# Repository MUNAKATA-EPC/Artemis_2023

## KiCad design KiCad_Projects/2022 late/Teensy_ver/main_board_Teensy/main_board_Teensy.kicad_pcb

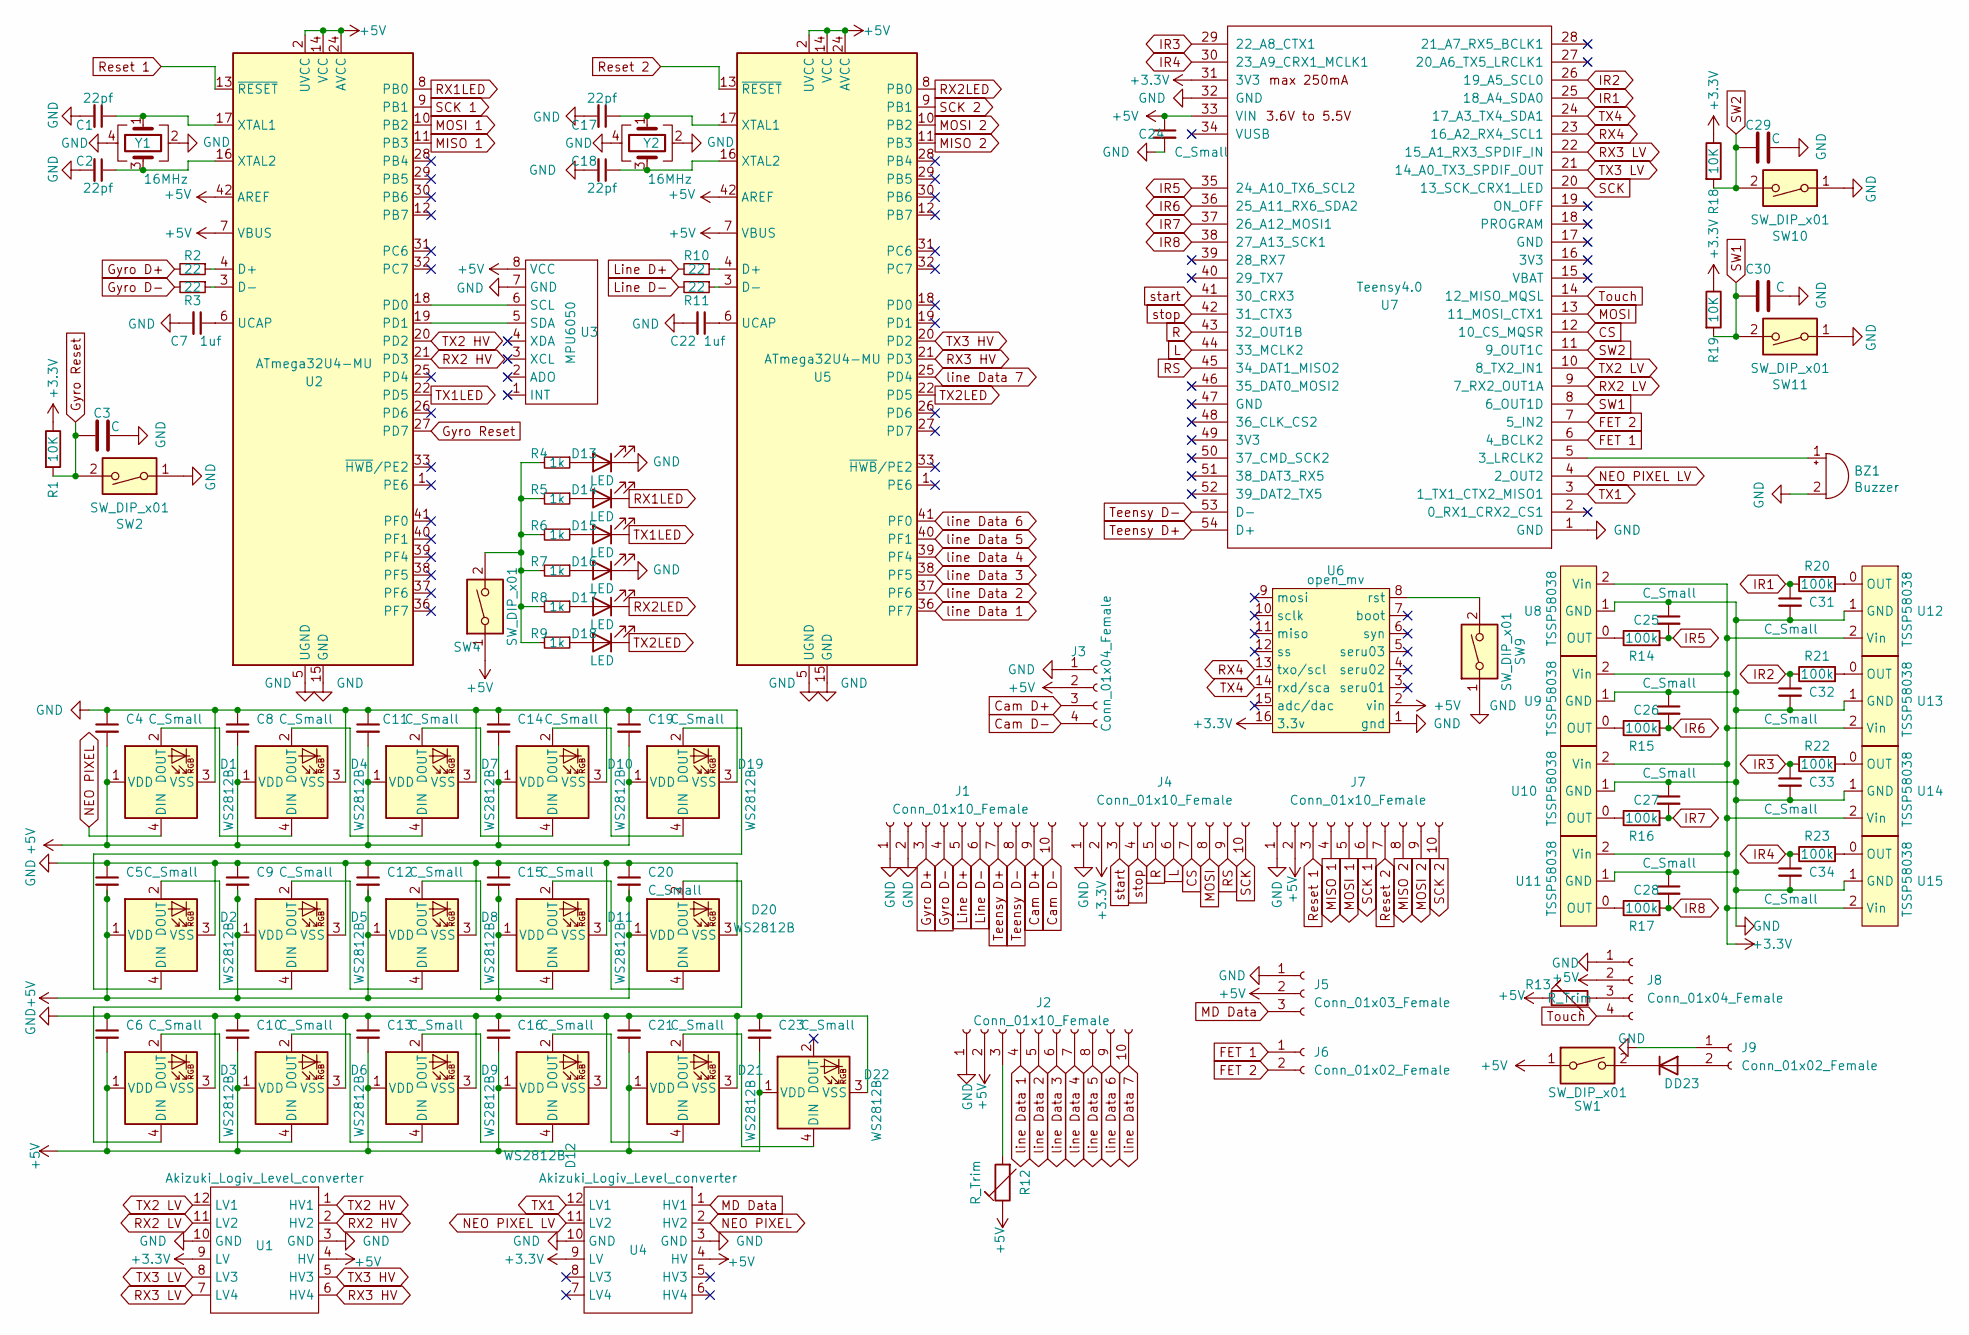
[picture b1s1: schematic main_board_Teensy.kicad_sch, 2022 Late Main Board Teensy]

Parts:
BZ1: Buzzer; Buzzer_12x9.5RM7.6
C1, C2, C17, C18: 22pf; C_0402_1005Metric; LCSC C1555
C3, C29, C30: C; C_0402_1005Metric; LCSC C507422
C4, C5, C6, C8, C9, C10, C11, C12, C13, C14, C15, C16, C19, C20, C21, C23, C24, C25, C26, C27, C28, C31, C32, C33, C34: C_Small; C_0402_1005Metric; LCSC C507422
C7, C22: 1uf; C_0402_1005Metric; LCSC C52923
D1, D2, D3, D5, D6, D7, D8, D9, D10, D11, D12, D19, D20, D21, D22: WS2812B; LED_WS2812B_PLCC4_5.0x5.0mm_P3.2mm; LCSC C2761795
D4: WS2812B; LED_WS2812B_PLCC4_5.0x5.0mm_P3.2mm
D13, D14, D15, D16, D17, D18: LED; LED_0402_1005Metric; LCSC C130725
D23: D; D_A-405_P7.62mm_Horizontal
J1, J4, J7: Conn_01x10_Female; PinHeader_1x10_P2.54mm_Vertical
J2: Conn_01x10_Female; JST_XH_S10B-XH-A-1_1x10_P2.50mm_Horizontal
J3: Conn_01x04_Female; PinHeader_1x04_P2.54mm_Vertical
J5: Conn_01x03_Female; JST_XH_B3B-XH-A_1x03_P2.50mm_Vertical
J6, J9: Conn_01x02_Female; JST_XH_B2B-XH-A_1x02_P2.50mm_Vertical
J8: Conn_01x04_Female; JST_XH_B4B-XH-A_1x04_P2.50mm_Vertical
R1, R18, R19: 10K; R_0402_1005Metric; LCSC C269674
R2, R3, R10, R11: 22; R_0402_1005Metric; LCSC C25092
R4, R5, R6, R7, R8, R9: 1k; R_0402_1005Metric; LCSC C11702
R12, R13: R_Trim; 可変抵抗(小)
R14, R15, R16, R17, R20, R21, R22, R23: 100k; R_0402_1005Metric; LCSC C269673
SW1, SW4: SW_DIP_x01; 2MS1T2B4M2QES
SW2, SW9, SW10, SW11: SW_DIP_x01; SW_PUSH_6mm_H5mm
U1, U4: Akizuki_Logiv_Level_converter; Akizuki_Logic_Level_converter
U2, U5: ATmega32U4-MU; QFN-44-1EP_7x7mm_P0.5mm_EP5.2x5.2mm; LCSC C112161
U3: MPU6050
U6: open_mv; OpenMV
U7: Teensy4.0; Teensy_Brakeout
U8, U9, U10, U11, U12, U13, U14, U15: TSSP58038; TSSP58038_IR
Y1, Y2: 16MHz; Crystal_SMD_3225-4Pin_3.2x2.5mm; LCSC C164049

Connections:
+3V3: J4.2, R1.1, R18.1, R19.1, U1.9 (LV), U4.9 (LV), U6.16 (3.3v), U7.31 (3V3), U8.2 (Vin), U9.2 (Vin), U10.2 (Vin), U11.2 (Vin), U12.2 (Vin), U13.2 (Vin), U14.2 (Vin), U15.2 (Vin)
+5V: C4.2, C5.2, C6.2, C8.2, C9.2, C10.2, C11.2, C12.2, C13.2, C14.2, C15.2, C16.2, C19.2, C20.2, C21.2, C23.2, C24.1, D1.1 (VDD), D2.1 (VDD), D3.1 (VDD), D4.1 (VDD), D5.1 (VDD), D6.1 (VDD), D7.1 (VDD), D8.1 (VDD), D9.1 (VDD), D10.1 (VDD), D11.1 (VDD), D12.1 (VDD), D19.1 (VDD), D20.1 (VDD), D21.1 (VDD), D22.1 (VDD), J2.2, J3.2, J5.2, J7.2, J8.2, R12.1, R13.1, SW1.1, SW4.1, U1.4 (HV), U2.2 (UVCC), U2.7 (VBUS), U2.14 (VCC), U2.24 (AVCC), U2.34 (VCC), U2.42 (AREF), U2.44 (AVCC), U3.8 (VCC), U4.4 (HV), U5.2 (UVCC), U5.7 (VBUS), U5.14 (VCC), U5.24 (AVCC), U5.34 (VCC), U5.42 (AREF), U5.44 (AVCC), U6.2 (vin), U7.33 (VIN)
CS: J4.7, U7.12 (10_CS_MQSR)
Cam D+: J1.9, J3.3
Cam D-: J1.10, J3.4
FET 1: J6.1, U7.6 (4_BCLK2)
FET 2: J6.2, U7.7 (5_IN2)
GND: BZ1.2 (+), C1.2, C2.2, C3.2, C4.1, C5.1, C6.1, C7.2, C8.1, C9.1, C10.1, C11.1, C12.1, C13.1, C14.1, C15.1, C16.1, C17.2, C18.2, C19.1, C20.1, C21.1, C22.2, C23.1, C24.2, C25.1, C26.1, C27.1, C28.1, C29.2, C30.2, C31.2, C32.2, C33.2, C34.2, D1.3 (VSS), D2.3 (VSS), D3.3 (VSS), D4.3 (VSS), D5.3 (VSS), D6.3 (VSS), D7.3 (VSS), D8.3 (VSS), D9.3 (VSS), D10.3 (VSS), D11.3 (VSS), D12.3 (VSS), D13.1 (K), D16.1 (K), D19.3 (VSS), D20.3 (VSS), D21.3 (VSS), D22.3 (VSS), J1.1, J1.2, J2.1, J3.1, J4.1, J5.1, J7.1, J8.1, J9.1, SW2.1, SW9.1, SW10.1, SW11.1, U1.3 (GND), U1.10 (GND), U2.5 (UGND), U2.15 (GND), U2.23 (GND), U2.35 (GND), U2.43 (GND), U2.45 (GND), U3.7 (GND), U4.3 (GND), U4.10 (GND), U5.5 (UGND), U5.15 (GND), U5.23 (GND), U5.35 (GND), U5.43 (GND), U5.45 (GND), U6.1 (gnd), U7.1 (GND), U7.32 (GND), U8.1 (GND), U9.1 (GND), U10.1 (GND), U11.1 (GND), U12.1 (GND), U13.1 (GND), U14.1 (GND), U15.1 (GND), Y1.2, Y1.4, Y2.2, Y2.4
Gyro D+: J1.3, R2.2
Gyro D-: J1.4, R3.2
Gyro Reset: C3.1, R1.2, SW2.2, U2.27 (PD7)
IR1: C31.1, R20.1, U7.25 (18_A4_SDA0)
IR2: C32.1, R21.1, U7.26 (19_A5_SCL0)
IR3: C33.1, R22.1, U7.29 (22_A8_CTX1)
IR4: C34.1, R23.1, U7.30 (23_A9_CRX1_MCLK1)
IR5: C25.2, R14.2, U7.35 (24_A10_TX6_SCL2)
IR6: C26.2, R15.2, U7.36 (25_A11_RX6_SDA2)
IR7: C27.2, R16.2, U7.37 (26_A12_MOSI1)
IR8: C28.2, R17.2, U7.38 (27_A13_SCK1)
L: J4.6, U7.44 (33_MCLK2)
Line D+: J1.5, R10.2
Line D-: J1.6, R11.2
MD Data: J5.3, U4.1 (HV1)
MISO 1: J7.4, U2.11 (PB3)
MISO 2: J7.8, U5.11 (PB3)
MOSI: J4.8, U7.13 (11_MOSI_CTX1)
MOSI 1: J7.5, U2.10 (PB2)
MOSI 2: J7.9, U5.10 (PB2)
NEO PIXEL: D1.4 (DIN), U4.2 (HV2)
NEO PIXEL LV: U4.11 (LV2), U7.4 (2_OUT2)
unnamed: BZ1.1 (-), U7.5 (3_LRCLK2)
unnamed: C1.1, U2.17 (XTAL1), Y1.1
unnamed: C2.1, U2.16 (XTAL2), Y1.3
unnamed: C7.1, U2.6 (UCAP)
unnamed: C17.1, U5.17 (XTAL1), Y2.1
unnamed: C18.1, U5.16 (XTAL2), Y2.3
unnamed: C22.1, U5.6 (UCAP)
unnamed: D1.2 (DOUT), D4.4 (DIN)
unnamed: D2.2 (DOUT), D5.4 (DIN)
unnamed: D3.2 (DOUT), D6.4 (DIN)
unnamed: D4.2 (DOUT), D7.4 (DIN)
unnamed: D5.2 (DOUT), D8.4 (DIN)
unnamed: D6.2 (DOUT), D9.4 (DIN)
unnamed: D10.2 (DOUT), D19.4 (DIN)
unnamed: D7.2 (DOUT), D10.4 (DIN)
unnamed: D11.2 (DOUT), D20.4 (DIN)
unnamed: D8.2 (DOUT), D11.4 (DIN)
unnamed: D12.2 (DOUT), D21.4 (DIN)
unnamed: D9.2 (DOUT), D12.4 (DIN)
unnamed: D13.2 (A), R4.1
unnamed: D14.2 (A), R5.1
unnamed: D15.2 (A), R6.1
unnamed: D16.2 (A), R7.1
unnamed: D17.2 (A), R8.1
unnamed: D18.2 (A), R9.1
unnamed: D2.4 (DIN), D19.2 (DOUT)
unnamed: D3.4 (DIN), D20.2 (DOUT)
unnamed: D21.2 (DOUT), D22.4 (DIN)
unnamed: D23.1 (K), SW1.2
unnamed: D23.2 (A), J9.2
unnamed: J2.3, R12.2
unnamed: J8.3, R13.2
unnamed: R2.1, U2.4 (D+)
unnamed: R3.1, U2.3 (D-)
unnamed: R4.2, R5.2, R6.2, R7.2, R8.2, R9.2, SW4.2
unnamed: R10.1, U5.4 (D+)
unnamed: R11.1, U5.3 (D-)
unnamed: R14.1, U8.0 (OUT)
unnamed: R15.1, U9.0 (OUT)
unnamed: R16.1, U10.0 (OUT)
unnamed: R17.1, U11.0 (OUT)
unnamed: R20.2, U12.0 (OUT)
unnamed: R21.2, U13.0 (OUT)
unnamed: R22.2, U14.0 (OUT)
unnamed: R23.2, U15.0 (OUT)
unnamed: U2.18 (PD0), U3.6 (SCL)
unnamed: U2.19 (PD1), U3.5 (SDA)
unnamed: SW9.2, U6.8 (rst)
R: J4.5, U7.43 (32_OUT1B)
RS: J4.9, U7.45 (34_DAT1_MISO2)
RX1LED: D14.1 (K), U2.8 (PB0)
RX2 HV: U1.2 (HV2), U2.21 (PD3)
RX2 LV: U1.11 (LV2), U7.9 (7_RX2_OUT1A)
RX2LED: D17.1 (K), U5.8 (PB0)
RX3 HV: U1.6 (HV4), U5.21 (PD3)
RX3 LV: U1.7 (LV4), U7.22 (15_A1_RX3_SPDIF_IN)
RX4: U6.13 (txo/scl), U7.23 (16_A2_RX4_SCL1)
Reset 1: J7.3, U2.13 (~RESET)
Reset 2: J7.7, U5.13 (~RESET)
SCK: J4.10, U7.20 (13_SCK_CRX1_LED)
SCK 1: J7.6, U2.9 (PB1)
SCK 2: J7.10, U5.9 (PB1)
SW1: C30.1, R19.2, SW11.2, U7.8 (6_OUT1D)
SW2: C29.1, R18.2, SW10.2, U7.11 (9_OUT1C)
TX1: U4.12 (LV1), U7.3 (1_TX1_CTX2_MISO1)
TX1LED: D15.1 (K), U2.22 (PD5)
TX2 HV: U1.1 (HV1), U2.20 (PD2)
TX2 LV: U1.12 (LV1), U7.10 (8_TX2_IN1)
TX2LED: D18.1 (K), U5.22 (PD5)
TX3 HV: U1.5 (HV3), U5.20 (PD2)
TX3 LV: U1.8 (LV3), U7.21 (14_A0_TX3_SPDIF_OUT)
TX4: U6.14 (rxd/sca), U7.24 (17_A3_TX4_SDA1)
Teensy D+: J1.7, U7.54 (D+)
Teensy D-: J1.8, U7.53 (D-)
Touch: J8.4, U7.14 (12_MISO_MQSL)
line Data 1: J2.4, U5.36 (PF7)
line Data 2: J2.5, U5.37 (PF6)
line Data 3: J2.6, U5.38 (PF5)
line Data 4: J2.7, U5.39 (PF4)
line Data 5: J2.8, U5.40 (PF1)
line Data 6: J2.9, U5.41 (PF0)
line Data 7: J2.10, U5.25 (PD4)
start: J4.3, U7.41 (30_CRX3)
stop: J4.4, U7.42 (31_CTX3)

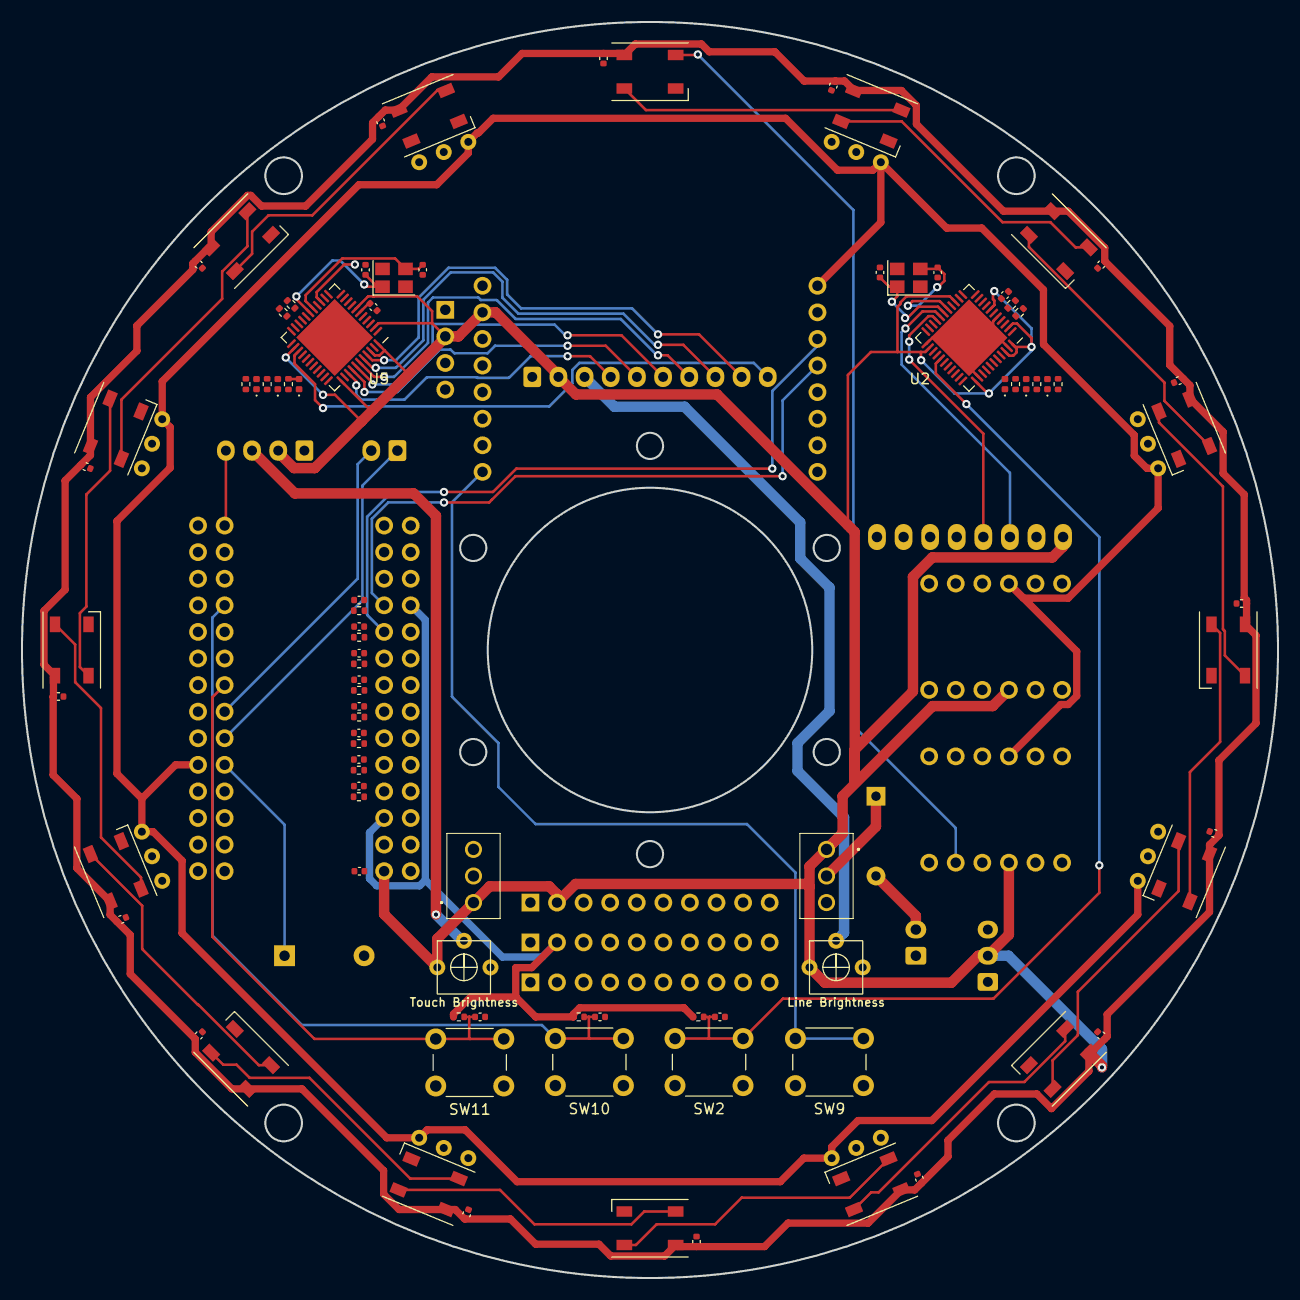
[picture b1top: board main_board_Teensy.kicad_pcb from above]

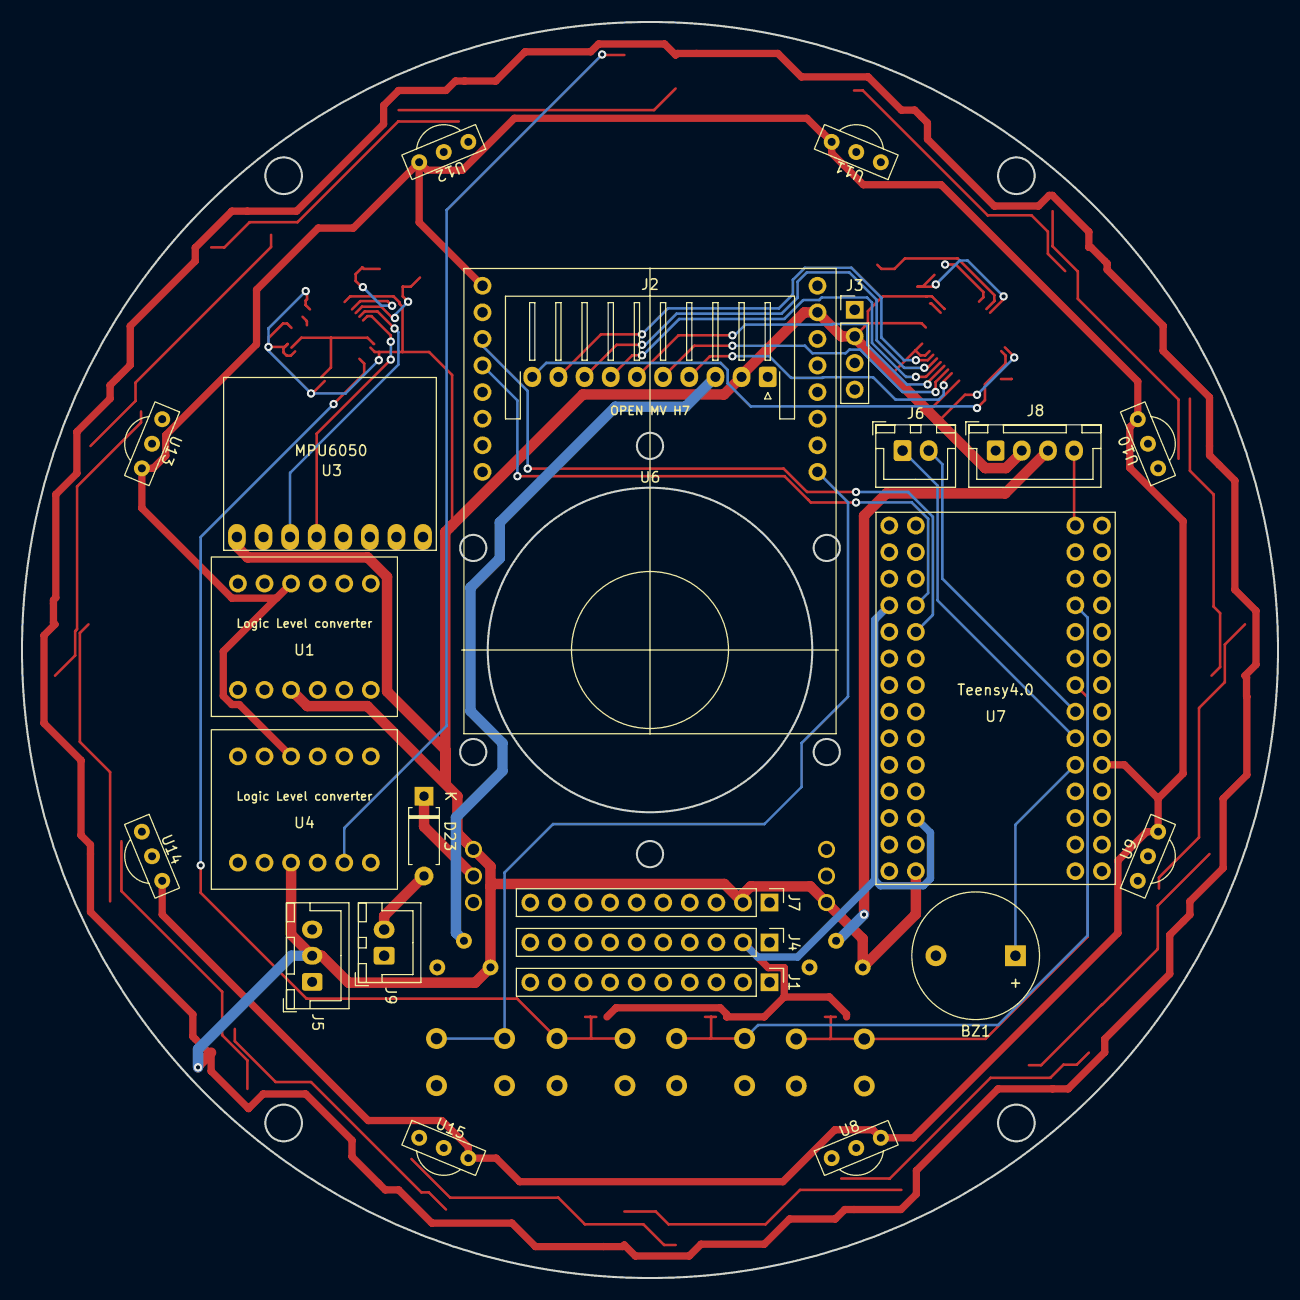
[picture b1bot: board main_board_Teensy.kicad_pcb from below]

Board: 2 copper layers, 120.0 x 120.0 mm, 113 parts (24 on the bottom side), 114 nets.

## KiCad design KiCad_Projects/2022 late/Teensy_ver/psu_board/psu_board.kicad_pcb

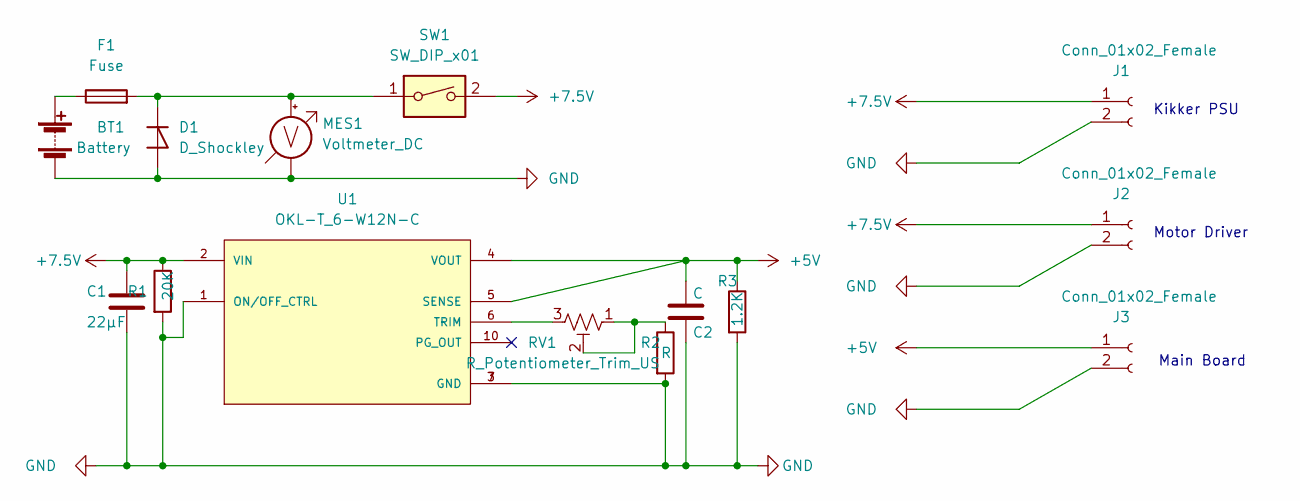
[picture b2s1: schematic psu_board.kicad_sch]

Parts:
BT1: Battery; JST_VH_B2P-VH-B_1x02_P3.96mm_Vertical
C1: 22μF; C_Disc_D5.1mm_W3.2mm_P5.00mm
C2: C; C_Disc_D5.1mm_W3.2mm_P5.00mm
D1: D_Shockley; D_5W_P12.70mm_Horizontal
F1: Fuse; fuse_socket
J1, J2, J3: Conn_01x02_Female; JST_XH_B2B-XH-A_1x02_P2.50mm_Vertical
MES1: Voltmeter_DC; voltage_counter
R1: 20K; R_Axial_DIN0204_L3.6mm_D1.6mm_P5.08mm_Horizontal
R2: R; R_Axial_DIN0204_L3.6mm_D1.6mm_P5.08mm_Horizontal
R3: 1.2K; R_Axial_DIN0204_L3.6mm_D1.6mm_P5.08mm_Horizontal
RV1: R_Potentiometer_Trim_US; Potentiometer_Bourns_3296W_Vertical
SW1: SW_DIP_x01; DS-850k
U1: OKL-T_6-W12N-C; DCDC-murata-6A

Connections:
+5V: C2.1, J3.1, R3.1, U1.4 (VOUT), U1.5 (SENSE)
+7.5V: C1.1, J1.1, J2.1, R1.1, SW1.2, U1.2 (VIN)
GND: BT1.2 (-), C1.2, C2.2, D1.2 (A), J1.2, J2.2, J3.2, MES1.1 (-), R1.2, R2.2, R3.2, U1.1 (ON/OFF_CTRL), U1.3 (GND), U1.7 (GND)
unnamed: BT1.1 (+), F1.1
unnamed: D1.1 (K), F1.2, MES1.2 (+), SW1.1
unnamed: R2.1, RV1.1, RV1.2
unnamed: RV1.3, U1.6 (TRIM)

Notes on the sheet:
Motor Driver
Kikker PSU
Main Board

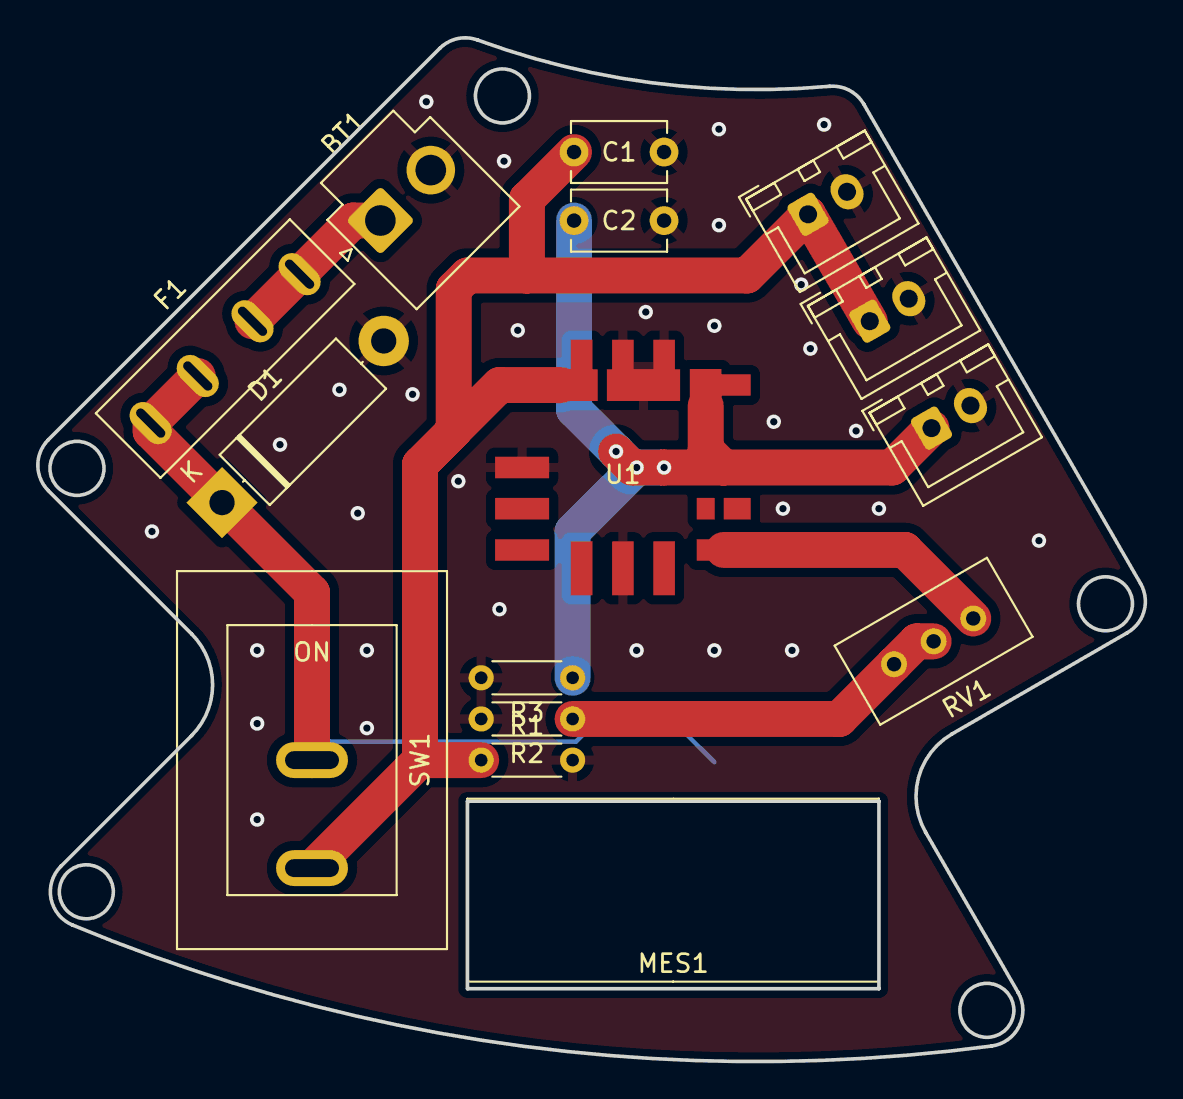
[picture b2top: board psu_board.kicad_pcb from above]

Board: 2 copper layers, 61.5 x 56.9 mm, 15 parts (0 on the bottom side), 7 nets.

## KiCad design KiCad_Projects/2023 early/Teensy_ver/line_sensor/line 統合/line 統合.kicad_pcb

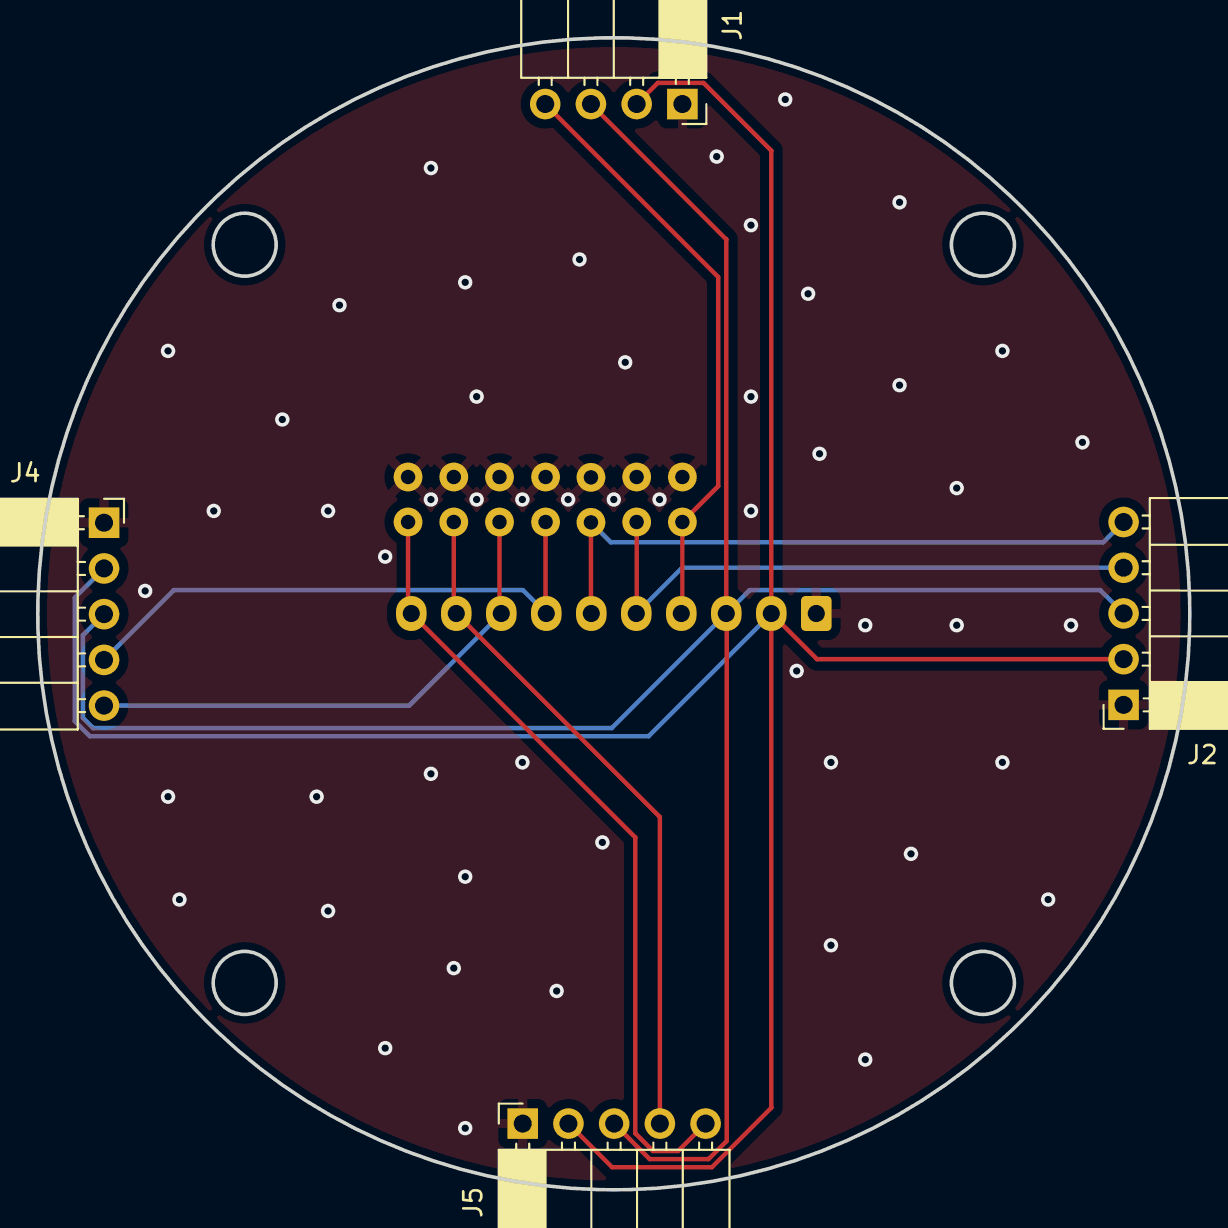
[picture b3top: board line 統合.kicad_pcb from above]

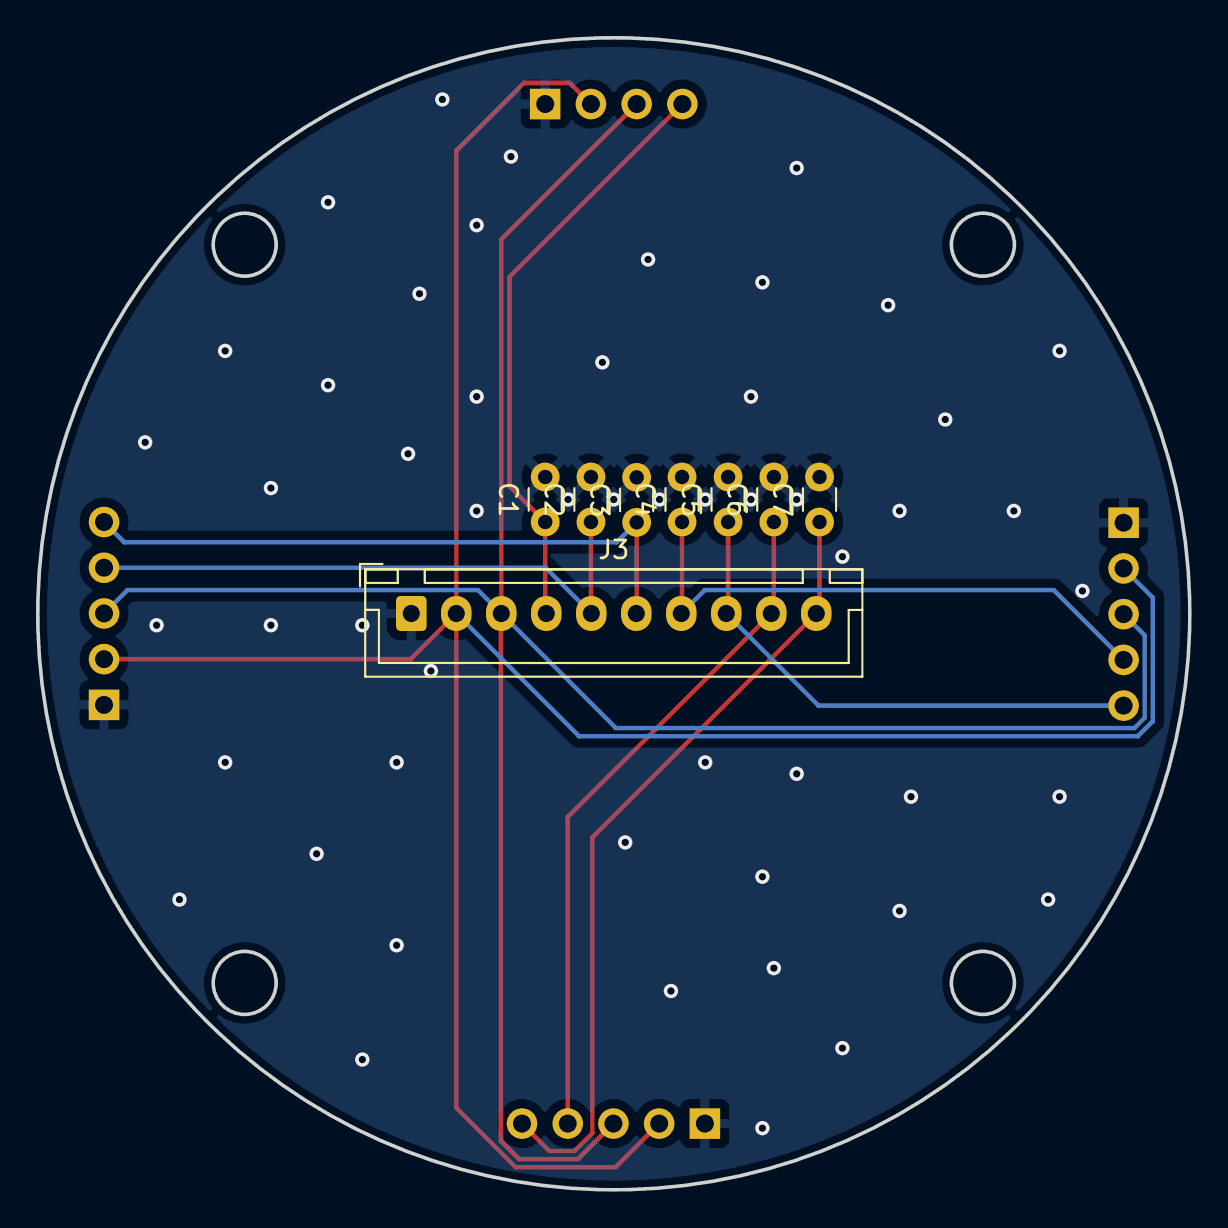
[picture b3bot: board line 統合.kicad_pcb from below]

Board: 2 copper layers, 64.0 x 64.0 mm, 12 parts (8 on the bottom side), 10 nets.

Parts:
C1, C2, C3, C4, C5, C6, C7: C_Small; C_Disc_D3.0mm_W1.6mm_P2.50mm
J1: Conn_01x04_Female; PinSocket_1x04_P2.54mm_Horizontal
J2, J4, J5: Conn_01x05_Female; PinSocket_1x05_P2.54mm_Horizontal
J3: Conn_01x10_Female; JST_XH_B10B-XH-A_1x10_P2.50mm_Vertical

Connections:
Line Left 1: C4.1, J3.7, J4.4
+5V: J1.2, J2.2, J3.2, J4.2, J5.2
GND: C1.2, C2.2, C3.2, C4.2, C5.2, C6.2, C7.2, J1.1, J2.1, J3.1, J4.1, J5.1
Line Back 1: C6.1, J3.9, J5.4
Line Back 2: C7.1, J3.10, J5.5
Line Front: C1.1, J1.4, J3.4
Line Left 2: C5.1, J3.8, J4.5
Line Right 1: C2.1, J2.4, J3.5
Line Right 2: C3.1, J2.5, J3.6
可変: J1.3, J2.3, J3.3, J4.3, J5.3

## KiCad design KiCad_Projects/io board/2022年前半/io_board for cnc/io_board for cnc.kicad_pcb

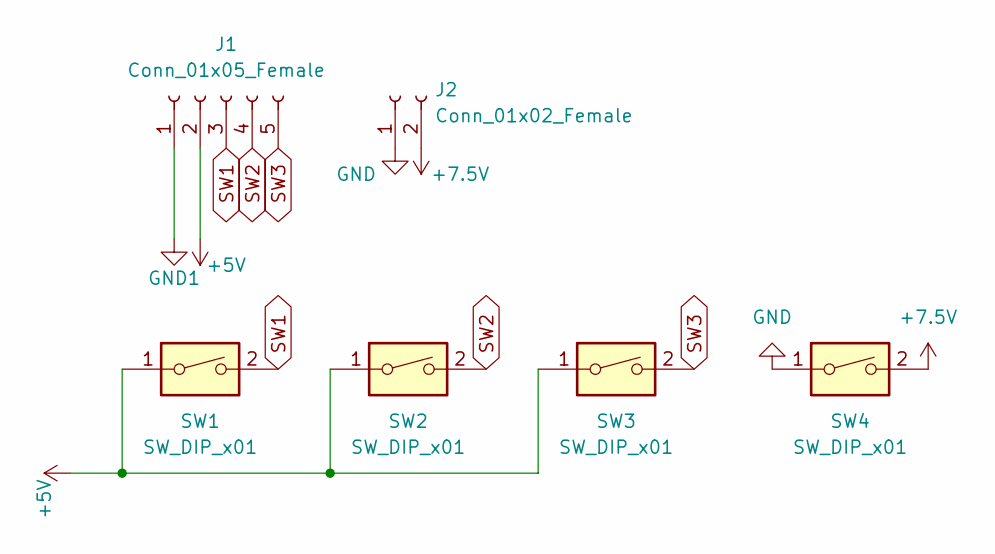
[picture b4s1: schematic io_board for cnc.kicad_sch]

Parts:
J1: Conn_01x05_Female; JST_XH_B5B-XH-A_1x05_P2.50mm_Vertical
J2: Conn_01x02_Female; JST_XH_B2B-XH-A_1x02_P2.50mm_Vertical
SW1, SW2, SW3: SW_DIP_x01; SW_PUSH_6mm_H5mm
SW4: SW_DIP_x01; DS-850k

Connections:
+5V: J1.2, SW1.1, SW2.1, SW3.1
+7.5V: J2.2, SW4.2
GND: J2.1, SW4.1
GND1: J1.1
SW1: J1.3, SW1.2
SW2: J1.4, SW2.2
SW3: J1.5, SW3.2

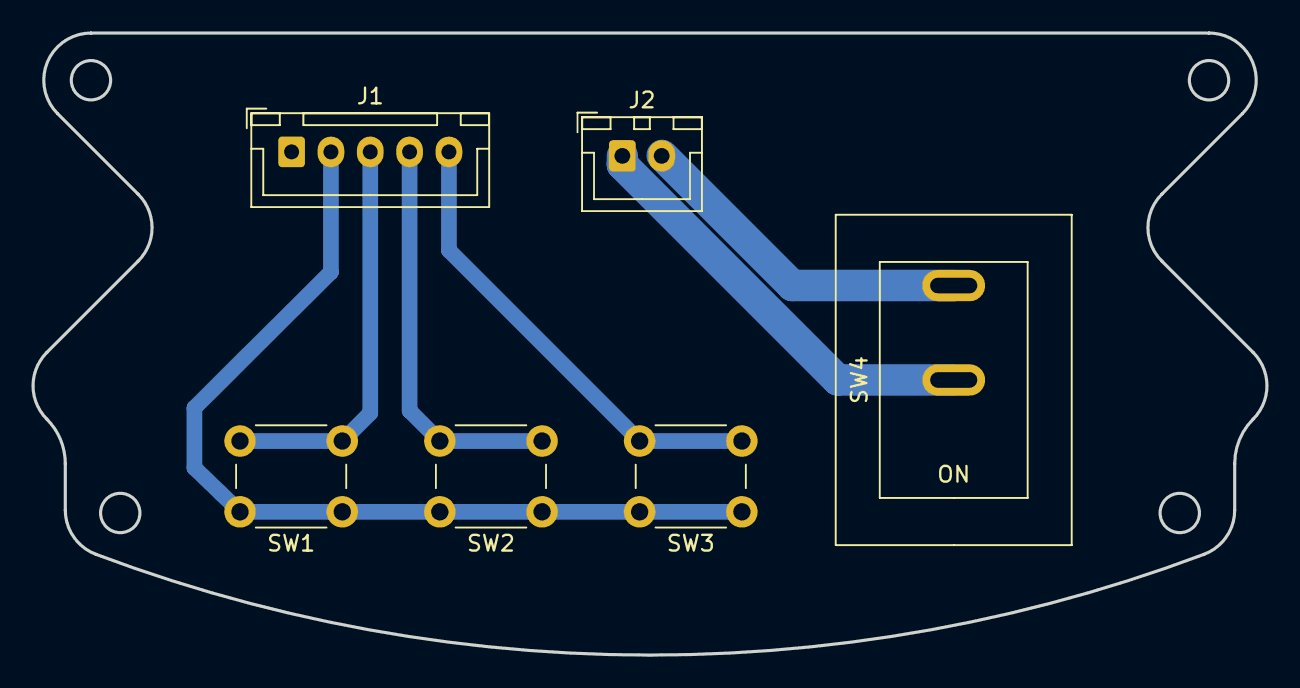
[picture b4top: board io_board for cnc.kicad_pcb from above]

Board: 2 copper layers, 78.4 x 39.5 mm, 6 parts (0 on the bottom side), 6 nets.
